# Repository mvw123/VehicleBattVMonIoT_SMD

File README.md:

Vehicle battery voltage monitor IoT SMD
=======================================

Vehicle battery voltage monitor IoT. Measures the voltage of a 12V car battery. Sends this to a receiver device which pushes the data to the cloud.

This PCB is designed to fit in the car strapped between the battery terminals. It uses either a LoRA RFM95 module, or a sub Ghz modules RFM69HCW module. Other parts of the design mostly use low cost modules to reduce the hand assembly time. Some through hole components, SMD 0805 and SMD diodes require hand assembly.

Designed using Eagle cad 7.5.0 light.

Incorporates support for:- 
* Arduino Pro Mini, 3.3V, 8MHz version only. (5V version will damage circuit)
* RFM69HCW or RFM95W/96W/97W/98W module
* SMA 50 ohm antenna connector
* 16 bit ADC module TI ADS1115
* Sensirion SHT31 temperature/humidity sensor module
* DC-DC converter
* Fuse and reverse voltage protection
* [Optional] RGB LED to visually indicate voltage levels
* [Optional] EUI-64 LoRA node identity chip for debug
* [Optional] Winbond flash storage
* [Optional] OLED display interface for debug purposes
* [Optional] HM-10 Bluetooth LE module carrier footprint

CAD B - [WIP]
=============

Not released yet, needs CAD updates. 

CAD A - [FAULTY]
===========================

Board has CAD issues, see issues list. needed some wiring and re-work. 
Board released for manufacture 3 Aug 2017
Software partially written

MVW
www.guvvy.co.uk

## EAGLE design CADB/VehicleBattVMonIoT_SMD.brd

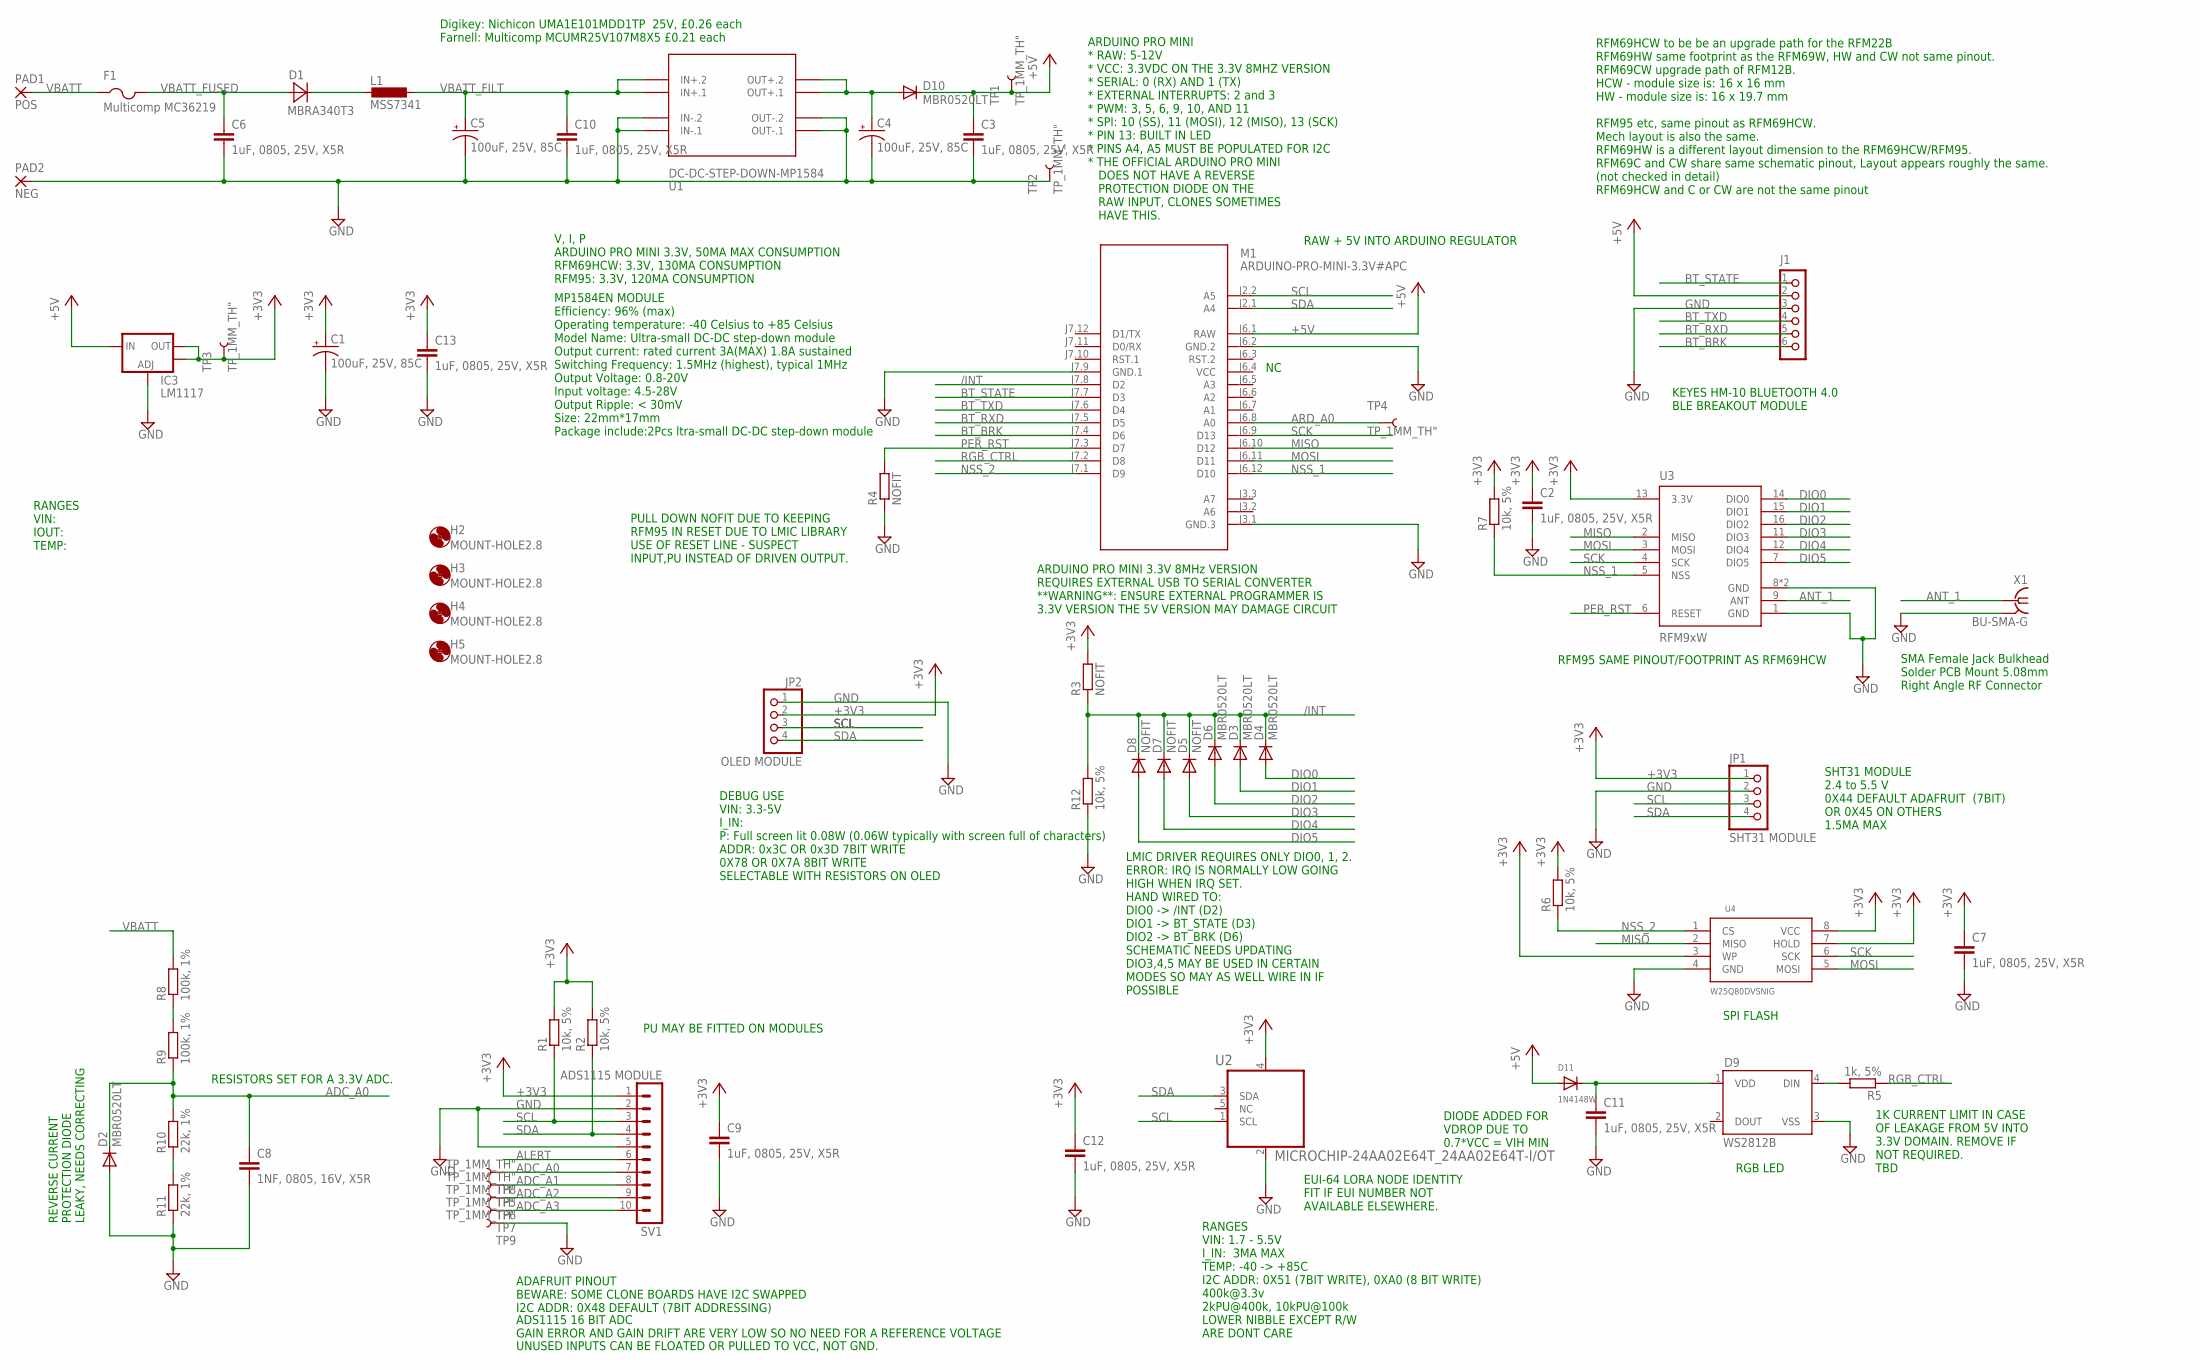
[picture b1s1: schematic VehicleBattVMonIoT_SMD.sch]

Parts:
C1, C4, C5: 100uF, 25V, 85C; CPOL-RADIAL-100UF-25V; MPN MCUMR25V107M8X5
C2, C3, C6, C7, C9, C10, C11, C12, C13: 1uF, 0805, 25V, X5R; C0805; MPN MC0805X105K250CT
C8: 1NF, 0805, 16V, X5R; C0805; MPN MCSH21B102K160CT
D1: MBRA340T3; SMA; MPN MBRA340T3G
D2, D3, D4, D6, D10: MBR0520LT; SOD123; MPN B0520LW-7-F
D5, D7, D8: NOFIT; SOD123; MPN B0520LW-7-F
D9: WS2812B
D11: 1N4148W; SOD-323F; MPN 1N4148WS.
F1: Multicomp MC36219; 1812; MPN MC36219.
H2, H3, H4, H5: MOUNT-HOLE2.8; 2,8
IC3: LM1117; SOT223; MPN LD1117S33TR
J1: HM-10 MODULE; M1X6_MALE_RIGHT_ANGLED_SMD
JP1: SHT31 MODULE; 1X04
JP2: OLED MODULE; 1X04
L1: MSS7341; MPN MSS7341-683MLD
M1: ARDUINO-PRO-MINI-3.3V#APC; ARDUINO-PRO-MINI#APC
PAD1: POS; 3,81/1,4
PAD2: NEG; 3,81/1,4
R1, R2, R6, R7, R12: 10k, 5%; R0805; MPN MC01W0805510K
R3, R4: NOFIT; R0805; MPN MC01W0805510K
R5: 1k, 5%; R0805; MPN WCR0805-1K0FI
R8, R9: 100k, 1%; R0805; MPN RC0805FR-07100KL
R10, R11: 22k, 1%; R0805; MPN WCR0805-22KFI
SV1: ADS1115 MODULE; MA10-1W
TP1, TP2, TP3, TP4, TP5, TP6, TP7, TP8, TP9: TP_1MM_TH"; TP_1MM_TH
U1: DC-DC-STEP-DOWN-MP1584
U2: MICROCHIP-24AA02E64T_24AA02E64T-I/OT; MICROCHIP-24AA02E64T_SOT95P270X145-5N
U3: RFM9xW; RFM69HCW-XXXS2
U4: W25Q80DVSNIG; SO08
X1: BU-SMA-G; MPN 5-1814400-1

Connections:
+3V3: C1.1 (+), C2.1, C7.1, C9.1, C12.1, C13.1, IC3.2 (OUT), IC3.4 (OUT), JP1.1, JP2.2, R1.2, R2.2, R3.2, R6.2, R7.2, SV1.1, TP3.P$1, U2.4 (VCC), U3.13 (3.3V), U4.3 (WP), U4.7 (HOLD), U4.8 (VCC)
+5V: C3.1, D10.C, D11.A, IC3.3 (IN), J1.2, M1.J6.1 (RAW), TP1.P$1
/INT: D3.C, D4.C, D5.C, D6.C, D7.C, D8.C, M1.J7.8 (D2), R3.1, R12.2
ADC_A0: C8.1, D2.C, R9.1, R10.2, SV1.7, TP8.P$1
ADC_A1: SV1.8, TP5.P$1
ADC_A2: SV1.9, TP6.P$1
ADC_A3: SV1.10, TP7.P$1
ALERT: SV1.6
ANT_1: U3.9 (ANT), X1.1
ARD_A0: M1.J6.8 (A0), TP4.P$1
BT_BRK: J1.6, M1.J7.4 (D6)
BT_RXD: J1.5, M1.J7.5 (D5)
BT_STATE: J1.1, M1.J7.7 (D3)
BT_TXD: J1.4, M1.J7.6 (D4)
DIO0: D4.A, U3.14 (DIO0)
DIO1: D3.A, U3.15 (DIO1)
DIO2: D6.A, U3.16 (DIO2)
DIO3: D5.A, U3.11 (DIO3)
DIO4: D7.A, U3.12 (DIO4)
DIO5: D8.A, U3.7 (DIO5)
GND: C1.2 (-), C2.2, C3.2, C4.2 (-), C5.2 (-), C6.2, C7.2, C8.2, C9.2, C10.2, C11.2, C12.2, C13.2, D2.A, D9.3 (VSS), IC3.1 (ADJ), J1.3, JP1.2, JP2.1, M1.J3.1 (GND.3), M1.J6.2 (GND.2), M1.J7.9 (GND.1), PAD2.1, R4.1, R11.1, R12.1, SV1.2, SV1.5, TP2.P$1, TP9.P$1, U1.IN-.1, U1.IN-.2, U1.OUT-.1, U1.OUT-.2, U2.2 (VSS), U3.1 (GND), U3.8 (GND), U3.10 (GND), U4.4 (GND), X1.2, X1.3 (2), X1.4 (2), X1.5 (2)
MISO: M1.J6.10 (D12), U3.2 (MISO), U4.2 (MISO)
MOSI: M1.J6.11 (D11), U3.3 (MOSI), U4.5 (MOSI)
unnamed: C11.1, D9.1 (VDD), D11.C
unnamed: D1.C, L1.1
unnamed: R10.1, R11.2
unnamed: R8.1, R9.2
unnamed: C4.1 (+), D10.A, U1.OUT+.1, U1.OUT+.2
unnamed: D9.4 (DIN), R5.2
NSS_1: M1.J6.12 (D10), R7.1, U3.5 (NSS)
NSS_2: M1.J7.1 (D9), R6.1, U4.1 (CS)
PER_RST: M1.J7.3 (D7), R4.2, U3.6 (RESET)
RGB_CTRL: M1.J7.2 (D8), R5.1
SCK: M1.J6.9 (D13), U3.4 (SCK), U4.6 (SCK)
SCL: JP1.3, JP2.3, M1.J2.2 (A5), R1.1, SV1.3, U2.1 (SCL)
SDA: JP1.4, JP2.4, M1.J2.1 (A4), R2.1, SV1.4, U2.3 (SDA)
VBATT: F1.1, PAD1.1, R8.2
VBATT_FILT: C5.1 (+), C10.1, L1.2, U1.IN+.1, U1.IN+.2
VBATT_FUSED: C6.1, D1.A, F1.2
VCC: M1.J6.4 (VCC)

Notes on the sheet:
RFM69HCW to be be an upgrade path for the RFM22B RFM69HW same footprint as the RFM69W, HW and CW not same pinout. RFM69CW upgrade path of RFM12B. HCW - module size is: 16 x 16 mm HW - module size is: 16 x 19.7 mm RFM95 etc, same pinout as RFM69HCW. Mech layout is also the same. RFM69HW is a differe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
ARDUINO PRO MINI 3.3V 8MHz VERSION REQUIRES EXTERNAL USB TO SERIAL CONVERTER **WARNING**: ENSURE EXTERNAL PROGRAMMER IS 3.3V VERSION THE 5V VERSION MAY DAMAGE CIRCUIT
ADS1115 16 BIT ADC GAIN ERROR AND GAIN DRIFT ARE VERY LOW SO NO NEED FOR A REFERENCE VOLTAGE
RFM95 SAME PINOUT/FOOTPRINT AS RFM69HCW
ADAFRUIT PINOUT BEWARE: SOME CLONE BOARDS HAVE I2C SWAPPED I2C ADDR: 0X48 DEFAULT (7BIT ADDRESSING)
ARDUINO PRO MINI * RAW: 5-12V * VCC: 3.3VDC ON THE 3.3V 8MHZ VERSION * SERIAL: 0 (RX) AND 1 (TX) * EXTERNAL INTERRUPTS: 2 and 3 * PWM: 3, 5, 6, 9, 10, AND 11 * SPI: 10 (SS), 11 (MOSI), 12 (MISO), 13 (SCK) * PIN 13: BUILT IN LED * PINS A4, A5 MUST BE POPULATED FOR I2C * THE OFFICIAL ARDUINO PRO MINI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
UNUSED INPUTS CAN BE FLOATED OR PULLED TO VCC, NOT GND.
MP1584EN MODULE Efficiency: 96% (max) Operating temperature: -40 Celsius to +85 Celsius Model Name: Ultra-small DC-DC step-down module Output current: rated current 3A(MAX) 1.8A sustained Switching Frequency: 1.5MHz (highest), typical 1MHz Output Voltage: 0.8-20V Input voltage: 4.5-28V Output Rippl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
V, I, P ARDUINO PRO MINI 3.3V, 50MA MAX CONSUMPTION RFM69HCW: 3.3V, 130MA CONSUMPTION RFM95: 3.3V, 120MA CONSUMPTION
REVERSE CURRENT PROTECTION DIODE LEAKY, NEEDS CORRECTING
KEYES HM-10 BLUETOOTH 4.0 BLE BREAKOUT MODULE
Digikey: Nichicon UMA1E101MDD1TP 25V, £0.26 each Farnell: Multicomp MCUMR25V107M8X5 £0.21 each
SHT31 MODULE 2.4 to 5.5 V 0X44 DEFAULT ADAFRUIT (7BIT) OR 0X45 ON OTHERS 1.5MA MAX
DEBUG USE VIN: 3.3-5V I_IN: P: Full screen lit 0.08W (0.06W typically with screen full of characters) ADDR: 0x3C OR 0x3D 7BIT WRITE 0X78 OR 0X7A 8BIT WRITE SELECTABLE WITH RESISTORS ON OLED
DIODE ADDED FOR VDROP DUE TO 0.7*VCC = VIH MIN
1K CURRENT LIMIT IN CASE OF LEAKAGE FROM 5V INTO 3.3V DOMAIN. REMOVE IF NOT REQUIRED. TBD
RANGES VIN: IOUT: TEMP:
SPI FLASH
RGB LED
EUI-64 LORA NODE IDENTITY FIT IF EUI NUMBER NOT AVAILABLE ELSEWHERE.
PU MAY BE FITTED ON MODULES
RANGES VIN: 1.7 - 5.5V I_IN: 3MA MAX TEMP: -40 -> +85C I2C ADDR: 0X51 (7BIT WRITE), 0XA0 (8 BIT WRITE) 400k@3.3v 2kPU@400k, 10kPU@100k LOWER NIBBLE EXCEPT R/W ARE DONT CARE
SMA Female Jack Bulkhead Solder PCB Mount 5.08mm Right Angle RF Connector
RAW + 5V INTO ARDUINO REGULATOR
LMIC DRIVER REQUIRES ONLY DIO0, 1, 2. ERROR: IRQ IS NORMALLY LOW GOING HIGH WHEN IRQ SET. HAND WIRED TO: DIO0 -> /INT (D2) DIO1 -> BT_STATE (D3) DIO2 -> BT_BRK (D6) SCHEMATIC NEEDS UPDATING DIO3,4,5 MAY BE USED IN CERTAIN MODES SO MAY AS WELL WIRE IN IF POSSIBLE
PULL DOWN NOFIT DUE TO KEEPING RFM95 IN RESET DUE TO LMIC LIBRARY USE OF RESET LINE - SUSPECT INPUT,PU INSTEAD OF DRIVEN OUTPUT.
RESISTORS SET FOR A 3.3V ADC.

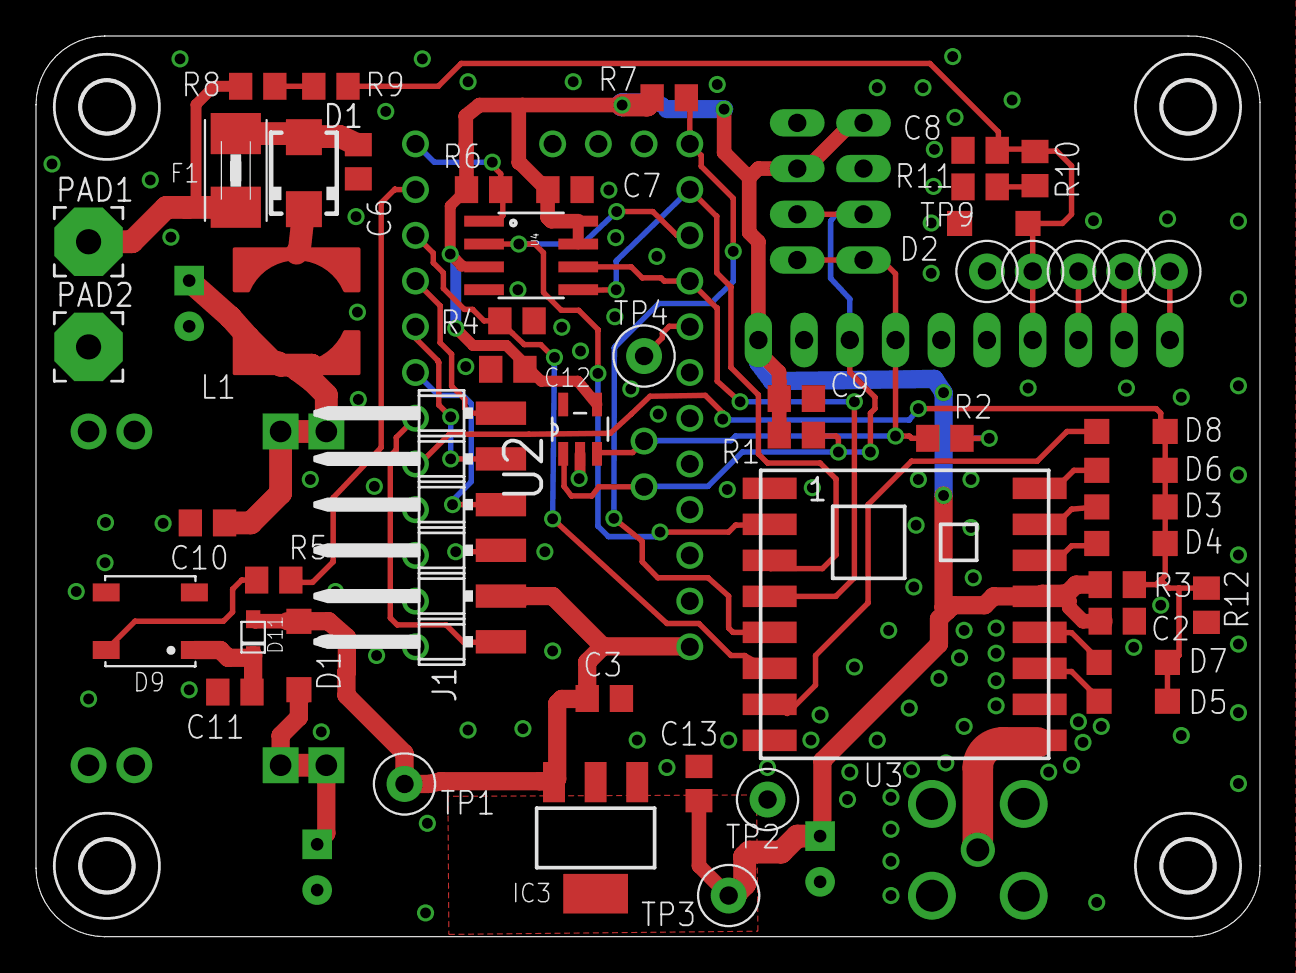
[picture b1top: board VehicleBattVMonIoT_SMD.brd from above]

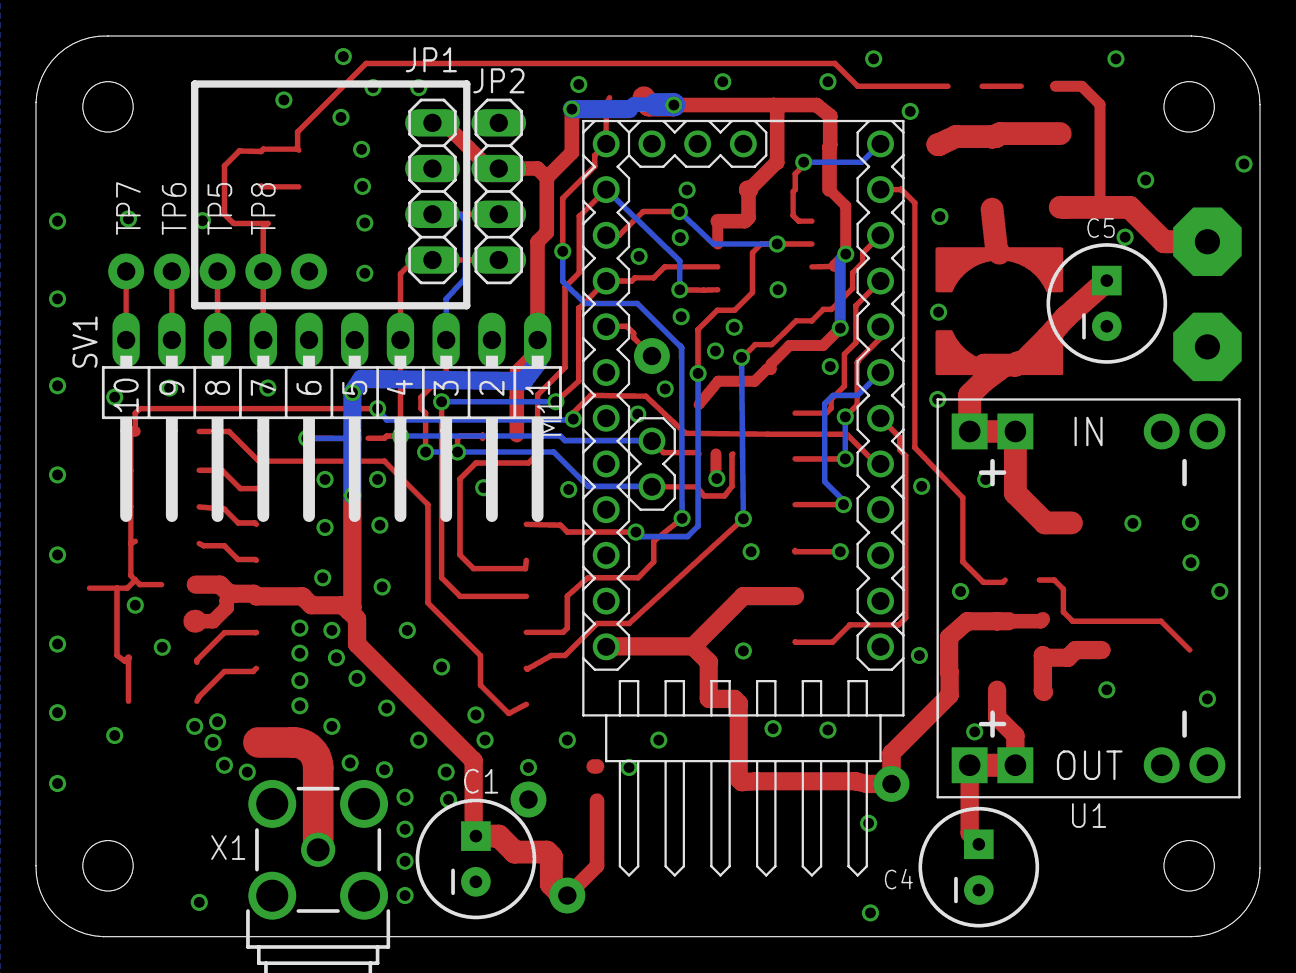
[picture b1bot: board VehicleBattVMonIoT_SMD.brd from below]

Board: 2 copper layers, 68.0 x 50.0 mm, 64 parts (9 on the bottom side), 38 nets.

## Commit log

2017-07-24 Vehicle battery voltage monitor IoT SMD version
    Vehicle battery voltage monitor IoT SMD version with two arduino pro
    mini boards, committing to backup before removing one
2017-07-24 updated arduino pro mini symbol to allow flood
2017-08-03 CAD A release for manufacture
    Released for manufacture at OSH park
2017-08-03 Added ReadMe file
    Added ReadMe file
2017-08-03 Minor updates
2017-08-03 Minor updates to schematic and pcb
2017-09-25 Latest CAD B and re-arrange structure
    seperate directory for CADA CADB.

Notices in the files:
parts and their libraries:
SparkFun-RF: Licensing: Creative Commons ShareAlike 4.0 International - https://creativecommons.org/licenses/by-sa/4.0
diy-modules: Released under the Creative Commons Attribution 4.0 International License: http://creativecommons.org/licenses/by/4.0
